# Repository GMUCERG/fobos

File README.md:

FOBOS
=====

Flexible Open-source workBench fOr Side-channel analysis (FOBOS) is an "acquisition to analysis" solution which includes all necessary software to control the device under test (attack) (DUT), trigger the oscilloscope, obtain the measurements and analyze them using several power analysis techniques.

FOBOS splits the Side Channel Analysis (SCA) setup into a control board, a DUT, and the SCA workstation. The firmware for the control board can be found in the folder `control`. The hardware description language files required to adapt a cryptographic algorithm to a particular FOBOS DUT are in the folder `DUT`. The `hardware` folder on the other hand contains circuit board design files for FOBOS boards such as the FOBOS Shield and several FOBOS DUTs. The `software` folder contains the scripts to run FOBOS. These python scripts run partially on the SCA workstation within a Jupyter notebook and partially on the Pynq DUT. The `docs` folder contains the FOBOS documentation.

Please cite as: 
```bibtex
@inproceedings{fobos3,
author = {Ferrufino, Eduardo and Beckwith, Luke and Abdulgadir, Abubakr and Kaps, Jens-Peter},
title = {{FOBOS} 3: An Open-Source Platform for Side-Channel Analysis and Benchmarking},
year = {2023},
isbn = {9798400702624},
publisher = {Association for Computing Machinery},
address = {New York, NY, USA},
url = {https://doi.org/10.1145/3605769.3623987},
doi = {10.1145/3605769.3623987},
pages = {5--14},
keywords = {hardware security, lightweight cryptography, side-channel analysis, benchmarking},
location = {, Copenhagen, Denmark, },
series = {ASHES '23}
}
```

FOBOS Control Board
-------------------
* `control`
   VHDL sources for configuring the FOBOS Control Boards. Requires Xilinx Vivado 2022.1.
   * `pynqctrl`
     Using a Digilent Inc PYNQ-Z1 or TUL PYNQ-Z2 as control board and either the FOBOS Shield or an oscilloscope for measurements.
   * `ip-repo` 
     Modules used by either control board.

FOBOS DUT
---------
* `dut`
  VHDL sources for FOBOS wrapper and pin assignments to prepare a DUT for instantiating a target algorithm.
  * `fpga_wrapper`
    Source code of the FOBOS wrapper common to all FPGA targets and the constraint files for the supported DUTs.
  * `example_cores`
    Contains implementations of example algorithms required for the tutorials.
 
FOBOS Hardware
--------------
* `hardware`
  Printed Circuit Board design files for FOBOS boards. Requires KiCad.
  * `fobos-shield`
    FOBOS Shield is a data aqcuisition and benchmarking boad that can be attached to the PYNQ-Z1 board.
  * `fobos-shield-Z2`
    FOBOS Shield is a data aqcuisition and benchmarking boad that can be attached to the PYNQ-Z2 board.
  * `fobos-mtc`
    FOBOS Multi Target Connector allows simple connection of DUT boards with PMOD connectors to the FOBOS Shield.
  * `fobos-dut`
    Contains folders for each FOBOS DUT.

FOBOS Software
--------------
* `software`
  FOBOS is controlled by a series of Python 3 scripts. 

  * `foboslib` contains all common FOBOS functions.
  * `notebooks` contains Jupyter notebooks that run within Jupyter Lab on the SCA workstation.
  * `lwc_tools` contains tools to make the GMU LWC Hardware API compatible with FOBOS.
  * `firmware` contains software that runs on FOBOS Control.

Documentation
-------------

* `docs` 
  Contains the sources for the Sphinx based documentation of FOBOS and the makefile to compile it.
  You can also read it at https://cryptography.gmu.edu/documentation/fobos3/index.html
  
License
-------

Copyright 2024 Cryptographic Engineering Research Group (CERG)

Licensed under the Apache License, Version 2.0 (the "License");
you may not use this file except in compliance with the License.
You may obtain a copy of the License at

    http://www.apache.org/licenses/LICENSE-2.0

Unless required by applicable law or agreed to in writing, software
distributed under the License is distributed on an "AS IS" BASIS,
WITHOUT WARRANTIES OR CONDITIONS OF ANY KIND, either express or implied.
See the License for the specific language governing permissions and
limitations under the License.

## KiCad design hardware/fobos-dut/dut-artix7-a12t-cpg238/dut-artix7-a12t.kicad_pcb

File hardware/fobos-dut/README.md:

FOBOS-DUT Boards
=========
  * `dut-artix7-a12t-cpg238`
    FOBOS FBD-A7 DUT with a Xilinx Artix-7 xc7a12tcpg238 device and power measurement circuitry.

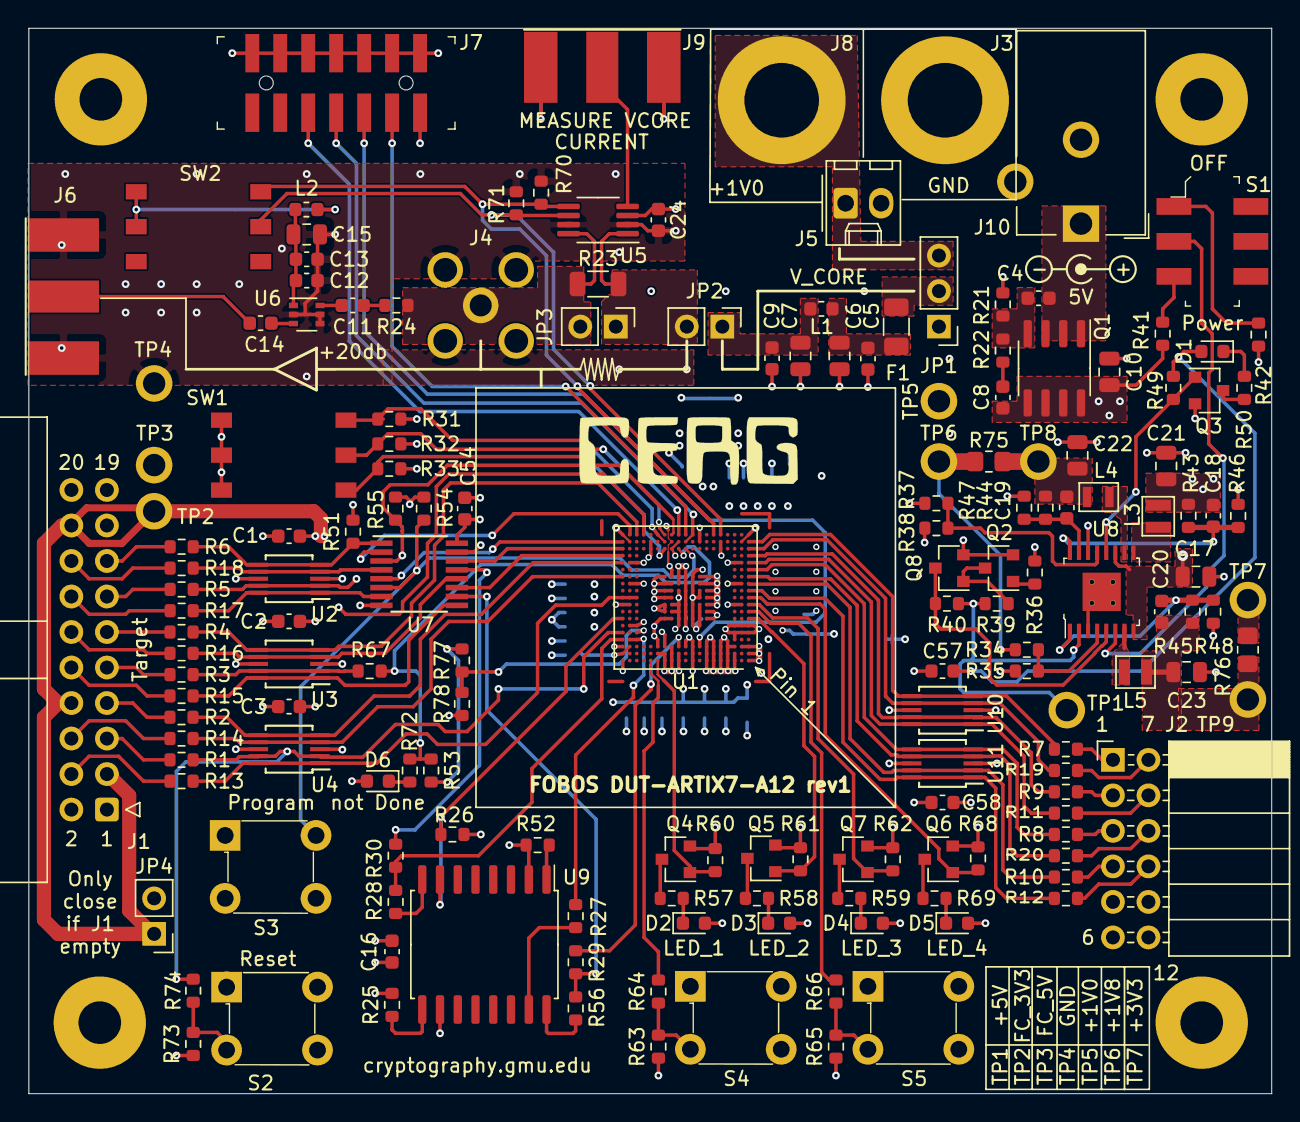
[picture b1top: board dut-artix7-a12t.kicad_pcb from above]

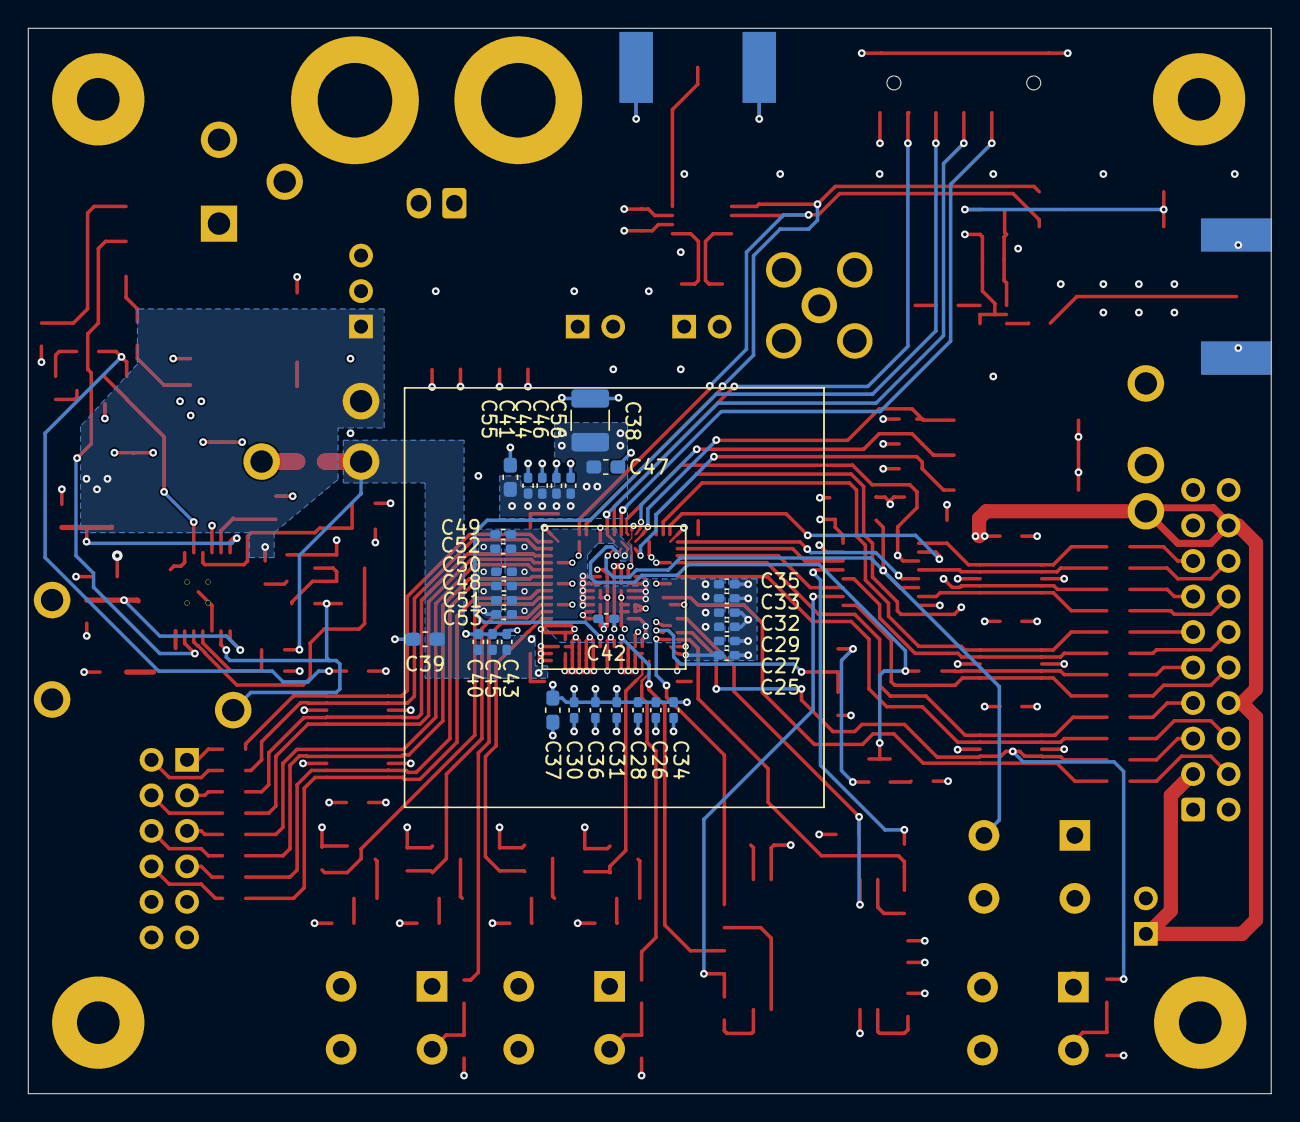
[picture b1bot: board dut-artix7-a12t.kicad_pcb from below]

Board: 4 copper layers, 88.9 x 76.2 mm, 201 parts (31 on the bottom side), 126 nets.

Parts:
C1, C2, C3, C4, C5, C9, C11, C13, C14, C16, C24, C54, C57, C58: 100nF; C_0603_1608Metric
C6, C10, C22, C23: 10uF; C_0805_2012Metric
C7: 47uF6.3V; C_0805_2012Metric
C8: 10nF; C_0603_1608Metric
C12: 4n7; C_0603_1608Metric
C15: 2u2; C_0805_2012Metric
C17, C21: 22uF; C_0805_2012Metric
C18, C19, C20: 20pF; C_0603_1608Metric
C25, C26, C27, C28, C40, C41, C48, C49: 4.7uF; C_0402_1005Metric_Pad0.74x0.62mm_HandSolder
C29, C30, C31, C32, C33, C34, C35, C36, C42, C43, C44, C45, C46, C50, C51, C52, C53, C56: .47uF; C_0402_1005Metric_Pad0.74x0.62mm_HandSolder
C37, C39, C47, C55: 47uF; C_0603_1608Metric_Pad1.08x0.95mm_HandSolder
C38: 100uF; C_1210_3225Metric_Pad1.33x2.70mm_HandSolder
D1, D2, D3, D4, D5, D6: LG_L29K-G2J1-24-Z; LED_0603_1608Metric
F1: MF-MSMF050-2; Fuse_1206_3216Metric
H1, H2, H3, H4: MountingHole; MH_4-40
J1: Target; IDC-Header_2x10_P2.54mm_Horizontal
J2: Pmod 2x6; PinSocket_2x06_P2.54mm_Horizontal_FLipped
J3, J8: 575-8
J4: Glitch; SMA-JOHNSON-142-0701-201
J5: Conn_01x02; Molex_KK-254_AE-6410-02A_1x02_P2.54mm_Vertical
J6, J9: Measure; SMA-JOHNSON-142-0701-801
J7: 0878321420; PinHeader_2x7_P2mm_SMD
J10: Barrel_Jack_Switch; BarrelJack_CUI_PJ-102AH_Horizontal
JP1: Source; PinHeader_1x03_P2.54mm_Vertical
JP2: CurProbe; PinHeader_1x02_P2.54mm_Vertical
JP3: Shunt1R; PinHeader_1x02_P2.54mm_Vertical
JP4: FC3V3_3V3_SHUNT; PinHeader_1x02_P2.54mm_Vertical
L1, L2: 1k/500mA; L_0603_1608Metric
L3: 1.5uH; L_SRN2012
L4: 3.3uH; L_BRC2012
L5: 2.2uH; L_SRN2012
Q1: FDS9435A; SOIC-8_3.9x4.9mm_P1.27mm
Q2, Q8: MMBT3904; SOT-23
Q3, Q4, Q5, Q6, Q7: BSS138; SOT-23
R1, R2, R3, R4, R5, R6, R13, R14, R15, R16, R17, R18: 22R; R_0603_1608Metric
R7, R8, R9, R10, R11, R12, R19, R20, R53, R72: 200R; R_0603_1608Metric
R21: 1M; R_0603_1608Metric
R22: 100R; R_0603_1608Metric
R23: 0R1; R_1206_3216Metric
R24: 49R9; R_0603_1608Metric
R25, R26, R31, R32, R33, R41, R52, R54, R55: 4.7KR; R_0603_1608Metric
R27, R28, R56: 33R; R_0603_1608Metric
R29, R30, R37, R67: 0R; R_0603_1608Metric
R34: 3.48KR; R_0603_1608Metric
R35, R42, R51, R60, R61, R62, R63, R64, R65, R66, R68, R70, R71, R73, R74: 10KR; R_0603_1608Metric
R36, R77, R78: 1KR; R_0603_1608Metric
R38, R39, R40, R49: 100KR; R_0603_1608Metric
R43: 30K; R_0603_1608Metric
R44: 150K; R_0603_1608Metric
R45: 180K; R_0603_1608Metric
R46, R47: 120KR; R_0603_1608Metric
R48: 57.6KR; R_0603_1608Metric
R50: 800R; R_0603_1608Metric
R57, R58, R59, R69: 470R; R_0603_1608Metric
R75, R76: 0.1R; R_0805_2012Metric_Pad1.20x1.40mm_HandSolder
S1: JS202011SCQN; Switch_Slide_JS202011SCQN
S2, S3, S4, S5: 1825910-6; Switch_Tactile_THT_6x6mm
SW1, SW2: SW_DIP_x03; DS04-254-2-03BK-SMT
TP1, TP2, TP3, TP4, TP5, TP6, TP7, TP8, TP9: 5281
U1: XC7A12T-CPG238; Xilinx_CPG238
U2, U3, U4, U10, U11: SP3003-04ATG; MSOP-10_3x3mm_P0.5mm
U5: INA225; MSOP-8_3x3mm_P0.65mm
U6: BGA2801; SOT-363_SC-70-6
U7: TS3A5018DBQR; SSOP-16_4.0x5.0mm_P0.635mm
U8: LTC3569EFE#PBF; TSSOP-16-1EP_W4.40mm
U9: IS25LP256D-JMLE; SOIC-16W_7.5x10.3mm_P1.27mm

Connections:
+1V0: C18.1, C21.1, JP1.1 (A), L3.2, R36.1, R43.2, TP5.1
+1V8: C39.1, C40.1, C43.1, C45.1, R34.2, R75.2, TP6.1, U1.C13, U1.H13, U1.J13
+3V3: C16.1, C25.1, C26.1, C27.1, C28.1, C29.1, C30.1, C31.1, C32.1, C33.1, C34.1, C35.1, C36.1, C37.1, C48.1, C49.1, C50.1, C51.1, C52.1, C53.1, J7.2, JP4.2 (B), R25.2, R26.2, R31.1, R32.1, R33.1, R52.2, R53.2, R54.2, R55.2, R76.2, R77.2, TP7.1, U1.B19, U1.C14, U1.C18, U1.G12, U1.G13, U1.J7, U1.K7, U1.K12, U1.K13, U1.L7, U1.L12, U1.L13, U1.M7, U1.M8, U1.M12, U1.M13, U1.N7, U1.N8, U1.N13, U1.U12, U1.V11, U9.2 (VCC)
+5V: C8.1, C10.1, C17.1, Q1.5 (D), Q1.6 (D), Q1.7 (D), Q1.8 (D), R37.2, R39.2, R40.2, R41.2, TP1.1, U8.2 (SVIN), U8.8 (PVIN1), U8.11 (PVIN2), U8.14 (RT)
/Connectors, IO/CW_HS1: J1.4, R13.2
/Connectors, IO/CW_HS2: J1.6, R14.2
/Connectors, IO/CW_MISO: J1.7, R2.1
/Connectors, IO/CW_MOSI: J1.9, R3.1
/Connectors, IO/CW_PDIC: J1.13, R5.1
/Connectors, IO/CW_PDID: J1.15, R6.1
/Connectors, IO/CW_RST: J1.5, R1.1
/Connectors, IO/CW_SCK: J1.11, R4.1
/Connectors, IO/CW_TARG1: J1.10, R15.2
/Connectors, IO/CW_TARG2: J1.12, R16.2
/Connectors, IO/CW_TARG3: J1.14, R17.2
/Connectors, IO/CW_TARG4: J1.16, R18.2
/FPGA 1/DIN: R28.1, R30.2, U1.D19
/FPGA 1/FCS: R26.1, U1.G19, U9.7 (CE#)
/FPGA 1/MOSI: R27.1, U1.D17, U1.D18
/FPGA 1/PUDC: R77.1, R78.2, U1.E17
/FPGA Programming/CCLK: R29.2, U1.C11
/FPGA Programming/MODE_1: R32.2, SW1.4, U1.W13
/FPGA Programming/MODE_2: R33.2, SW1.6, U1.U13
/FPGA Programming/TCK: J7.6, U1.C8
/FPGA Programming/TDI: J7.10, U1.W11
/FPGA Programming/TMS: J7.4, U1.W10
/Power/EN2: Q8.3 (C), R40.1, U8.5 (EN2)
/Power/EN3: R34.1, R35.2, U8.4 (EN3)
/Power/FB1: C18.2, R43.1, R46.1, U8.16 (FB1)
/Power/FB2: C19.2, R44.1, R47.1, U8.15 (FB2)
/Power/FB3: C20.2, R45.1, R48.1, U8.1 (FB3)
/Power/MODE: R37.1, R38.2, U8.13 (MODE)
/Power/SW1: L3.1, U8.9 (SW1)
/Power/SW2: L4.1, U8.10 (SW2)
/Power/SW3: L5.1, U8.7 (SW3)
/Power/pre1V8: C19.1, C22.1, L4.2, R44.2, R75.1, TP8.1
/Power/pre3V3: C20.1, C23.1, L5.2, R45.2, R76.1, TP9.1
FC2D_CLK: R14.1, U1.N19, U4.4 (IO3)
FC2D_HS: R4.2, U1.W17, U3.5 (IO4)
FC_3V3: C1.2, C2.2, C3.2, C24.1, C54.1, C57.2, C58.2, D1.2 (A), D2.2 (A), D3.2 (A), D4.2 (A), D5.2 (A), J1.3, J1.8, J1.18, J2.6, J2.12, JP4.1 (A), L2.1, R49.1, S2.1, S4.1, S5.1, SW2.4, SW2.6, TP2.1, U2.3 (VCC), U3.3 (VCC), U4.3 (VCC), U5.3 (Vs), U7.16 (V+), U10.3 (VCC), U11.3 (VCC)
FC_5V: C4.1, J1.1, J1.20, J10.1, Q1.1 (S), Q1.2 (S), Q1.3 (S), TP3.1
FC_DIO0: R15.1, U3.1 (IO1), U7.9 (COM3)
FC_DIO0_MUX: U1.T19, U7.11 (NC3)
FC_DIO1: R16.1, U3.4 (IO3), U7.12 (COM4)
FC_DIO1_MUX: U1.U19, U7.14 (NC4)
FC_DIO2: R17.1, U2.1 (IO1), U7.7 (COM2)
FC_DIO2_MUX: U1.V19, U7.5 (NC2)
FC_DIO3: R18.1, U2.4 (IO3), U7.4 (COM1)
FC_DIO3_MUX: U1.W18, U7.2 (NC1)
FC_IO: R2.2, U1.R19, U4.5 (IO4)
FC_PROG: R6.2, R51.2, U2.5 (IO4), U7.1 (IN)
FC_RST: R1.2, R74.2, U1.E19, U4.2 (IO2)
FD2C_CLK: R13.1, U1.K17, U1.K18, U1.K19, U4.1 (IO1)
FD2C_HS: R5.2, U1.W16, U2.2 (IO2)
FD_TF: R3.2, R67.1, U3.2 (IO2)
GND: C1.1, C2.1, C3.1, C5.2, C6.2, C7.2, C9.2, C10.2, C12.2, C13.2, C15.2, C16.2, C17.2, C21.2, C22.2, C23.2, C24.2, C25.2, C26.2, C27.2, C28.2, C29.2, C30.2, C31.2, C32.2, C33.2, C34.2, C35.2, C36.2, C37.2, C38.2, C39.2, C40.2, C41.2, C42.2, C43.2, C44.2, C45.2, C46.2, C47.2, C48.2, C49.2, C50.2, C51.2, C52.2, C53.2, C54.2, C55.2, C56.2, C57.1, C58.1, D6.2, J1.2, J1.17, J1.19, J2.5, J2.11, J3.1, J4.2 (Ext), J5.2, J6.2 (Ext), J7.1, J7.3, J7.5, J7.7, J7.9, J7.11, J7.13, J9.2 (Ext), J10.2, Q2.2 (E), Q3.2 (S), Q4.2 (S), Q5.2 (S), Q6.2 (S), Q7.2 (S), Q8.2 (E), R21.1, R35.1, R38.1, R42.1, R46.2, R47.2, R48.2, R51.1, R60.1, R61.1, R62.1, R63.1, R65.1, R68.1, R70.1, R71.1, R73.1, R78.1, S3.4, SW1.1, SW1.3, SW1.5, TP4.1, U1.A1, U1.A3, U1.A4, U1.A5, U1.A6, U1.A7, U1.A9, U1.A11, U1.A12, U1.A13, U1.A19, U1.B1, U1.B3, U1.B4, U1.B5, U1.B6, U1.B7, U1.B9, U1.B11, U1.B12, U1.B13, U1.B14, U1.C1, U1.C2, U1.C3, U1.C4, U1.C5, U1.C6, U1.C7, U1.C9, U1.C10, U1.C12, U1.C19, U1.D3, U1.E1, U1.E2, U1.E3, U1.F1, U1.F2, U1.F3, U1.F17, U1.F18, U1.G7, U1.G8, U1.G9, U1.G11, U1.H7, U1.H8, U1.H9, U1.H11, U1.H12, U1.J2, U1.J3, U1.J8, U1.J9, U1.J11, U1.J12, U1.J18, U1.J19, U1.K8, U1.L8, U1.L9, U1.L11, U1.M2, U1.M3, U1.M9, U1.M17, U1.M18, U1.N9, U1.N12, U1.R2, U1.R3, U1.R17, U1.R18, U1.U5, U1.U15, U1.V2, U1.V5, U1.V8, U1.V12, U1.V15, U1.V18, U1.W1, U1.W8, U1.W19, U2.8 (GND), U3.8 (GND), U4.8 (GND), U5.2 (GND), U5.7 (Ref), U6.2 (G), U6.4 (G), U6.5 (G), U7.8 (GND), U7.15 (EN#), U8.3 (SGND), U8.17 (EPAD), U9.10 (GND), U10.8 (GND), U11.8 (GND)
JA1: R7.2, U1.V1, U10.5 (IO4)
JA2: R9.2, U1.T1, U10.2 (IO2)
JA3: R8.2, U1.P1, U11.5 (IO4)
JA4: R10.2, U1.M1, U11.2 (IO2)
JA7: R19.1, U1.U1, U10.4 (IO3)
JA8: R11.1, U1.R1, U10.1 (IO1)
JA9: R20.1, U1.N1, U11.4 (IO3)
JA10: R12.1, U1.L1, U11.1 (IO1)
MODE_0: R31.2, SW1.2, U1.V13, U1.W14
unnamed: C5.1, C6.1, F1.1, L1.2
unnamed: C8.2, R22.1
unnamed: C11.1, U6.6
unnamed: C11.2, R24.1
unnamed: C14.2, U6.3
unnamed: D1.1 (K), R50.1
unnamed: D2.1 (K), R57.1
unnamed: D3.1 (K), R58.1
unnamed: D4.1 (K), R59.1
unnamed: D5.1 (K), R69.1
unnamed: D6.1, R72.1
unnamed: J2.1, R7.1
unnamed: J2.2, R9.1
unnamed: J2.3, R8.1
unnamed: J2.4, R10.1
unnamed: J2.7, R19.2
unnamed: J2.8, R11.2
unnamed: J2.9, R20.2
unnamed: J2.10, R12.2
unnamed: J5.1, J8.1, JP1.3 (B)
unnamed: C14.1, J6.1 (In)
unnamed: F1.2, JP1.2 (C)
unnamed: C7.1, C9.1, JP2.1 (A), L1.1
unnamed: JP2.2 (B), JP3.1 (A), R23.2, U5.1 (Vin+)
unnamed: C4.2, Q1.4 (G), R21.2, R22.2
unnamed: Q2.1 (B), R36.2
unnamed: Q2.3 (C), Q8.1 (B), R39.1
unnamed: Q3.3 (D), R50.2
unnamed: Q4.3 (D), R57.2
unnamed: Q5.3 (D), R58.2
unnamed: Q6.3 (D), R69.2
unnamed: Q7.3 (D), R59.2
unnamed: R41.1, S1.3
unnamed: R42.2, S1.1
unnamed: R63.2, R64.1, S4.3
unnamed: R65.2, R66.1, S5.3
unnamed: R73.2, R74.1, S2.3
unnamed: C12.1, C13.1, C15.1, L2.2, U6.1 (Vcc)
unnamed: R52.1, U9.1 (HOLD#)
unnamed: R56.2, U9.16 (SCK)
unnamed: R27.2, U9.15 (SI)
unnamed: R28.2, U9.8 (SO)
unnamed: R25.1, U9.9 (WP#)
ON_OFF: S1.2, U8.6 (EN1)
PGOOD: Q3.1 (G), R49.2, U8.12 (PGOOD)
SW_CLK: R29.1, R56.1, U7.10 (NO3)
SW_DIN: R30.1, U7.13 (NO4)
SW_DONE: R53.1, R67.2, R72.2, U1.U11
SW_INIT_B: R55.1, U1.W12, U7.3 (NO1)
SW_PROGRAM_B: R54.1, S3.2, U1.U10, U7.6 (NO2)
TDO: J7.8, U1.V10, U1.W9
USER_BTN_1: R64.2, U1.A15
USER_BTN_2: R66.2, U1.H1
USER_LED_1: Q4.1 (G), R60.2, U1.A14
USER_LED_2: Q5.1 (G), R61.2, U1.G1
USER_LED_3: Q7.1 (G), R62.2, U1.J1
USER_LED_4: Q6.1 (G), R68.2, U1.K1
VCCINT: C38.1, C41.1, C42.1, C44.1, C46.1, C47.1, C55.1, C56.1, J4.1 (In), JP3.2 (B), R23.1, R24.2, U1.G10, U1.H10, U1.J10, U1.L10, U1.M10, U1.M11, U1.N10, U1.N11, U5.8 (Vin-)
VCORE_CURRENT: J9.1 (In), U5.4 (Out)
VCORE_CURRENT_GAIN_0: R70.2, SW2.5, U1.W6, U5.5 (GS0)
VCORE_CURRENT_GAIN_1: R71.2, SW2.3, U1.W5, U5.6 (GS1)

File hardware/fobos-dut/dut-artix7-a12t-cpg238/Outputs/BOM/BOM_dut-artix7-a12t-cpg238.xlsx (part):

Artix-7 DUT
Ref# | Qty. | Value | Size | Mouser # | Mfr. # | Manufacturer | Description
R29 R30 R37 R67 | 4 | 0R | 0603 | 603-RC0603JR-070RL | RC0603JR-070RL | Yageo | Thick Film Resistors - SMD 0 Ohms 100 mW 0603 5%
R23 | 1 | 0R1 | 1206 | 71-WSL1206R1000DEA | WSL1206R1000DEA | Vishay | Current Sense Resistors - SMD 1/4watt .1ohms .5%
R24 | 1 | 49R9 | 0603 | 652-CR0603FX-49R9ELF | CR0603-FX-49R9ELF | Bourns | Thick Film Resistors - SMD 49.9 ohm 1%
R75 R76 | 2 | 0R1 | 0805 | 588-KDV08FR100ET | KDV08FR100ET | Ohmite | Current Sense Resistors - SMD 0.1 ohm 0805 1% 0.25W
R22 | 1 | 100R | 0603 | 603-RC0603FR-13100RL | RC0603FR-13100RL | Yageo | Thick Film Resistors - SMD 100 OHM 1%
R36 R77 R78 | 3 | 1k | 0603 | 603-RC0603FR-071KL | RC0603FR-071KL | Yageo | Thick Film Resistors - SMD 1K OHM 1%
R35 R42 R43 R44 R45 R51 R60 R61 R62 R63 R64 R65 R66 R68 R70 R71 R73 R74 | 18 | 10k | 0603 | 603-RC0603FR-0710KL | RC0603FR-0710KL | Yageo | Thick Film Resistors - SMD 10K OHM 1%
R38 R39 R40 R49 | 4 | 100k | 0603 | 652-CR0603-FX-103ELF | CR0603-FX-1003ELF | Bourns | Thick Film Resistors - SMD 100K 1% 1/10 WATT
R21 | 1 | 1M | 0603 | 652-CR0603FX-1004ELF | CR0603-FX-1004ELF | Bourns | Thick Film Resistors - SMD 1M 1% 1/10W
R46 R47 | 2 | 120k | 0603 | 603-RC0603FR-13120KL | RC0603FR-13120KL | Yageo | Thick Film Resistors - SMD 120 kOhms 100-200 mW 0603 1%
R7 R8 R9 R10 R11 R12 R19 R20 R53 R72 | 10 | 200R | 0603 | 603-RC0603FR-07200RL | RC0603FR-07200RL | Yageo | Thick Film Resistors - SMD 200 OHM 1%
R1 R2 R3 R4 R5 R6 R13 R14 R15 R16 R17 R18 | 12 | 22R | 0603 | 603-RC0603FR-0722RL | RC0603FR-0722RL | Yageo | Thick Film Resistors - SMD 22 OHM 1%
R27 R28 R56 | 3 | 33R, 0.5% | 0603 | 667-ERA-3AHD330V | ERA-3AHD330V | Panasonic | Thin Film Resistors - SMD 0603 33ohms 50ppm 0.5% AEC-Q200
R34 | 1 | 3k48 | 0603 | 603-RC0603FR-073K48L | RC0603FR-073K48L | Yageo | Thick Film Resistors - SMD 3.48 kOhms 100mW 0603 1%
R57 R58 R59 R69 | 4 | 470R | 0603 | 603-RC0603FR-10470RL | RC0603FR-10470RL | Yageo | Thick Film Resistors - SMD 470 OHM 1%
R25 R26 R31 R32 R33 R41 R52 R54 R55 | 9 | 4k7 | 0603 | 603-RC0603FR-134K7L | RC0603FR-134K7L | Yageo | Thick Film Resistors - SMD 4.7 kOhms 100-200mW 0603 1%
R48 | 1 | 57k6 | 0603 | 652-CR0603FX-5762ELF | CR0603-FX-5762ELF | Bourns | Thick Film Resistors - SMD 57.6K ohm 1%
R50 | 1 | 800R | 0603 | 603-RC0603FR-07806RL | RC0603FR-07806RL | Yageo | Thick Film Resistors - SMD 806 Ohms 100 mW 0603 1%
C8 | 1 | 10nF | 0603 | 603-CS0603KRX79BB103 | CS0603KRX7R9BB103 | Yageo | Multilayer Ceramic Capacitors MLCC - SMD/SMT 10 nF 50 V 10% Ceramic Capacitors
C1 C2 C3 C4 C5 C9 C11 C13 C14 C16 C24 C54 C57 C58 | 14 | 100nF | 0603 | 77-VJ0603Y104JXQPBC | VJ0603Y104JXQPW1BC | Vishay / Vitramon | Multilayer Ceramic Capacitors MLCC - SMD/SMT 0603 0.1uF 10volts X7R 5%
C6 C10 C22 C23 | 4 | 10uF | 0805 | 81-GRM21BC81C106MA3L | GRM21BC81C106MA73L | Murata Electronics | Multilayer Ceramic Capacitors MLCC - SMD/SMT 0805 10uF 16volts X6S 20%
C18 C19 C20 | 3 | 20pF | 0603 | 80-C0603C200K8HACTU | C0603C200K8HACTU | KEMET | Multilayer Ceramic Capacitors MLCC - SMD/SMT 10V 20pF X8R 0603 10%
C15 | 1 | 2u2F | 0805
C17 C21 | 2 | 22uF | 0805 | 187-CL21A226KQCLRNC | CL21A226KQCLRNC | Samsung | Multilayer Ceramic Capacitors MLCC - SMD/SMT 22uF+/-10% 6.3V X5R 2012
C12 | 1 | 4n7F | 0603 | 710-885012206087 | 885012206087 | Wurth Electronics | Multilayer Ceramic Capacitors MLCC - SMD/SMT WCAP-CSGP 4700pF 0603 10% 50V MLCC
C29 C30 C31 C32 C33 C34 C35 C36 C42 C43 C44 C45 C46 C50 C51 C52 C53 C56 | 18 | 470nF | 0402 | 963-JMK105BJ474KV-F | JMK105BJ474KV-F | Taiyo Yuden | CAP CER 0.47UF 6.3V X5R 0402
C25 C26 C27 C28 C40 C41 C48 C49 | 8 | 4.7uF | 0402 | 81-GRM155R60J475ME8J | GRM155R60J475ME87J | Murata Electronics | CAP CER 4.7UF 6.3V X5R 0402
C37 C39 C47 C55 | 4 | 47uF | 0603 | 81-GRM21BR60J476ME5K | GRM21BR60J476ME15K | Murata Electronics | Multilayer Ceramic Capacitors MLCC - SMD/SMT 0805 47uF 6.3volts
C7 | 1 | 47uF | 0805 | 81-GRT21BR60J476ME3L | GRT21BR60J476ME13L | Murata Electronics | Multilayer Ceramic Capacitors MLCC - SMD/SMT 47UF 6.3V 20% 0805
C38 | 1 | 100uF | 1210 | 81-GRM32ER61A107ME0L | GRM32ER61A107ME0L | Murata Electronics | Multilayer Ceramic Capacitors MLCC - SMD/SMT 1210 100uF 10V
L1 L2 | 2 | 1k/500mA | 0603 | 963-FBMH1608HM102-T | FBMH1608HM102-T | Taiyo Yuden | Ferrite Beads HI CUR CHIP BD 0603 1000OHMS 25%
L3 | 1 | 1.5uH |  | 652-SRN2012-1R5M | SRN2012-1R5M | Bourns Inc. | FIXED IND 1.5UH 1.8A 108MOHM SMD
L4 | 1 | 3.3uH |  | 963-BRC2012T3R3MD | BRC2012T3R3MD | Taiyo Yuden | FIXED IND 3.3UH 870MA 221MOHM SM
L5 | 1 | 2.2uH |  | 652-SRN2010-2R2M | SRN2010-2R2M | Bourns Inc. | FIXED IND 2.2UH 1.7A 170MOHM SMD
D1 D2 D3 D4 D5 D6 | 6 | green | 0603 | 604-APT1608CGCK | APT1608CGCK | Kingbright | Standard LEDs - SMD Green Water Clear 570nm 40mcd 120deg
Q3 Q4 Q5 Q6 Q7 | 5 | BSS138L | SOT-23-3 | 512-BSS138L | BSS138L | ON Semiconductor | MOSFET 0.20A, 50V N-Channel SOT-23 MOSFET
Q1 | 1 | FDS9435A | SOIC-8 | 512-FDS9435A | FDS9435A | ON Semiconductor/Fairchild | MOSFET SO-8 SGL P-CH -30V
Q2 Q8 | 2 | 3904 | SOT-23-3 | 863-MMBT3904LT1G | MMBT3904LT1G | ON Semiconductor | Bipolar Transistors - BJT NPN GENERAL PURPOSE
U8 | 1 | LTC3569EFE#PBF | 16TSSOP | LTC3569EFE#PBF | LTC3569EFE#PBF | Analog Devices Inc. | Switching Voltage Regulators Programmable 1.2A and 2X600mA, Triple Buck Regulat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
U5 | 1 | INA225 | MSOP-8 | 595-INA225AIDGKT | INA225AIDGKT | Texas Instruments | Current Sense Amplifiers 36V Bidir 0-Drift Ser Crnt-Shunt Mon
U7 | 1 | TS3A5018DBQR | 16SSOP | 595-TS3A5018DBQR | TS3A5018DBQR | Texas Instruments | Analog Switch ICs 10-Ohm Quad SPDT Analog Switch
U9 | 1 | IS25LP256D-JMLE | 16SOIC | IS25LP256D-JMLE | IS25LP256D-JMLE | ISSI, Integrated Silicon Solution Inc | NOR Flash 256M 3V 166MHZ Serial Flash
U6 | 1 | BGA2801 | SOT-363 | 771-BGA2801115 | BGA2801,115 | NXP USA Inc. | RF Amplifier 6CH MMIC Amp 3.8 dB 3.3V 14.3mA 2.8GHz
U1 | 1 | XC7A12T-cpg238 | CPG238 | 217-XC7A12T-1CPG238C | XC7A12T-1CPG238C | Xilinx | FPGA - Field Programmable Gate Array XC7A12T-1CPG238C
F1 | 1 | MF-MSMF050-2 | 1206 | 667-ERB-RG2R00V | ERB-RG2R00V | Panasonic Electronic Components | FUSE BOARD MOUNT 2A 63VDC 1206
U2 U3 U4 U10 U11 | 5 | Fuse | MSOP-10 | 576-SP3003-04ATG | SP3003-04ATG | Littelfuse | ESD Suppressors / TVS Diodes 4 Ch 8kV 0.65pF SPA
J10 | 1 | Barrel Jack |  | 490-PJ-102AH | PJ-102AH | CUI | DC Power Connectors Power Jacks
J4 | 1 | SMA Edge |  | 530-142-0701-801 | 142-0701-801 | Johnson / Cinch Connectivity Solutions | RF Connectors / Coaxial Connectors PC END MT JCK GLD .062" BOARD THICK
J6 J9 | 2 | SMA Vertical |  | 712-CONSMA008-G | CONSMA008-G | Linx Technologies | RF Connectors / Coaxial Connectors SMA Female PCB Mnt, Extended, Gold
J1 | 1 | Shrd Hdr | 2x10 | 517-30320-5002 | 30320-5002HB | 3M Electronic Solutions Division | Headers & Wire Housings 20P R/A 4WALL GLDFL
JP1, JP2, JP3, JP4 | 1 | Pin Header | 1x36 | 649-68001-236HLF | 68001-236HLF | Amphenol FCI | Headers & Wire Housings 36P HDR
J5 | 1 | Molex | 1x2-P2.54mm | 538-22-11-2022 | 22-11-2022 | Molex | Connector_Molex:Molex_KK-254_AE-6410-02A_1x02_P2.54mm_Vertical, gold
J7 | 1 | Shrd Hdr | 2x7 2mm | 538-87832-1420 | 878321420 | Molex | Headers & Wire Housings 14P SMD PB FREE SHRD
J3 J8 | 2 | 575-8 |  | 534-575-8 | 575-8 | Keystone Electronics | CONN BANANA JACK SOLDER
J2 | 1 | Pin Socket | 2x6 90 deg | 200-SSW10602FDRA | SSW-106-02-F-D-RA | Samtec | Board to Board & Mezzanine Connectors Tiger Buy Socket Strip with PCB Tails, 0.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
TP1 TP2 TP3 TP4 TP5 TP6 TP7 TP8 TP9 | 9 | 5281 |  | 534-5281 | 5281 | Keystone Electronics | Circuit Board Hardware - PCB TEST POINT BLACK MULTIPURPOSE
S1 | 1 | JS202011SCQN |  | 611-JS202011SCQN | JS202011SCQN | C&K | SWITCH SLIDE DPDT 300MA 6V
S2 S3 S4 S5 | 4 | 1825910-6 |  |  | 1825910-6 | TE Connectivity ALCOSWITCH Switches | SWITCH TACTILE SPST-NO 0.05A 24V
SW1 SW2 | 2 | SW_DIP_x03 |  | 490-DS04254203BK-SMT | DS04-254-2-03BK-SMT | CUI Devices | DIP SWITCH, SPST, 2.54 PITCH, FL
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
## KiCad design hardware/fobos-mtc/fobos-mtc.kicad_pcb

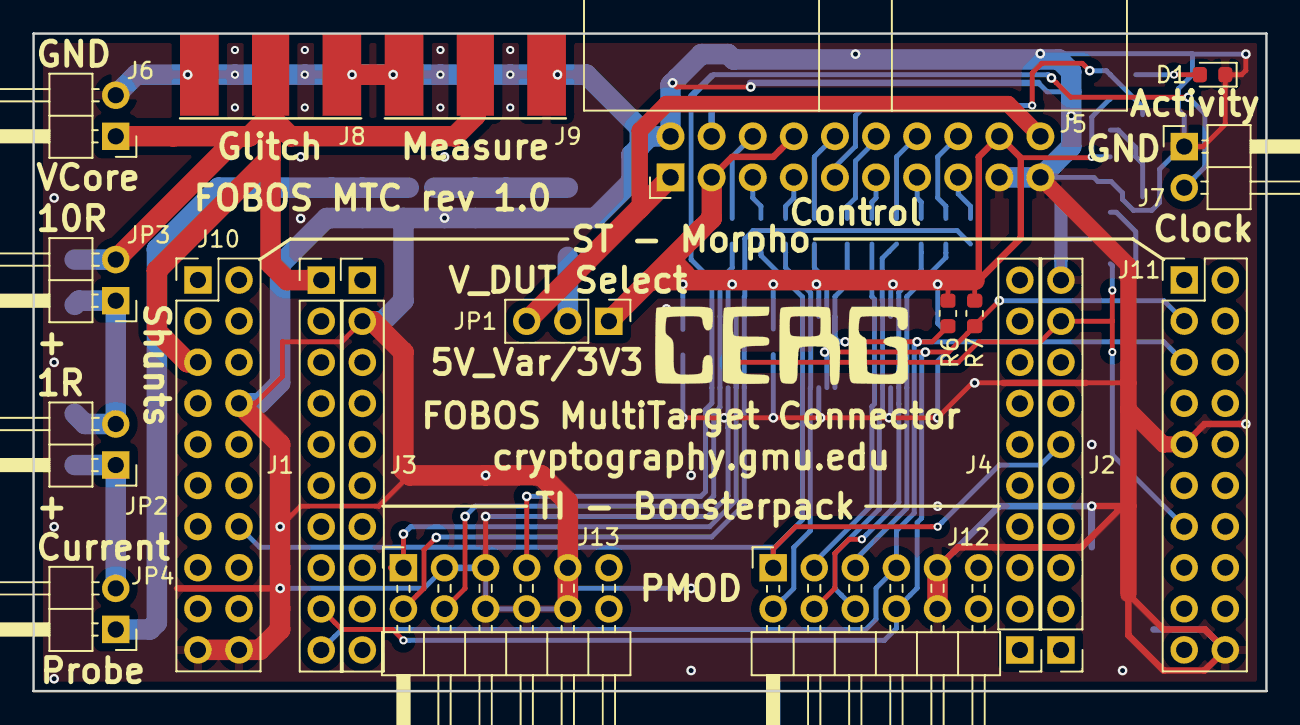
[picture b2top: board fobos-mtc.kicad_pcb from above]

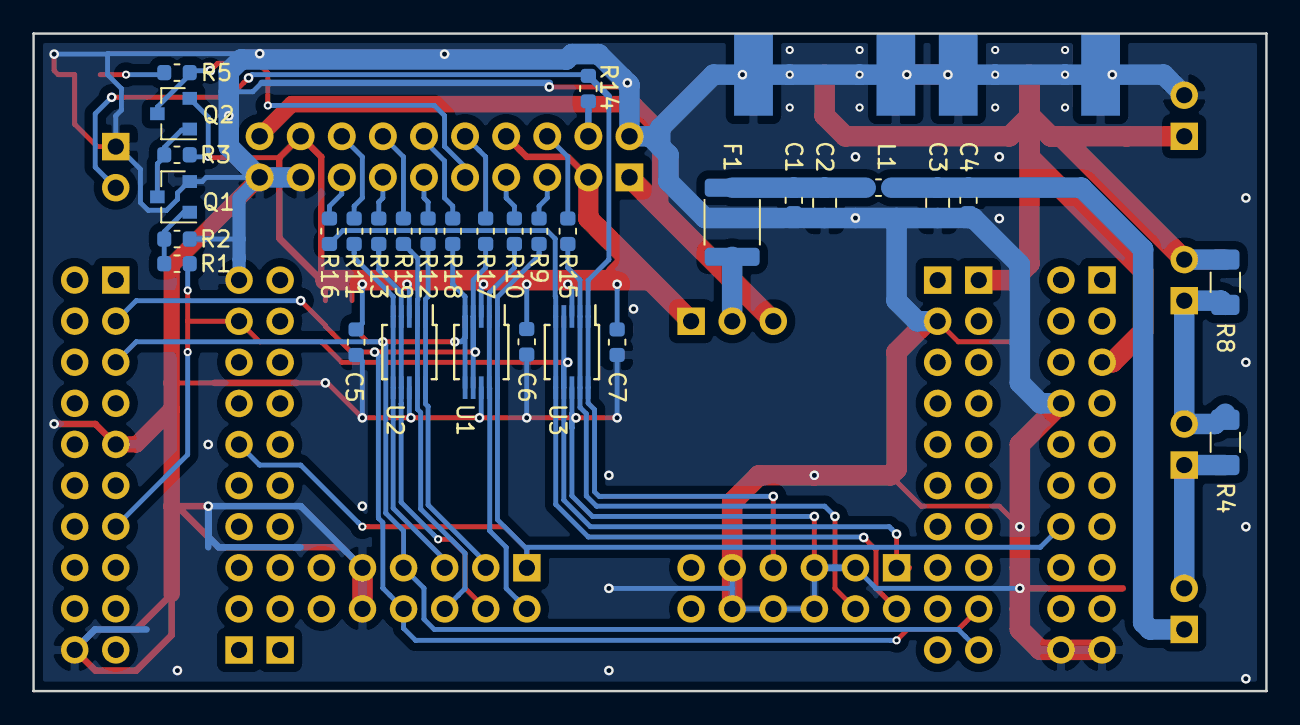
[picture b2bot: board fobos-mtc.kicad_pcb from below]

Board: 2 copper layers, 76.2 x 40.6 mm, 51 parts (31 on the bottom side), 36 nets.

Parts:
C1, C4, C5, C6, C7: 100nF; C_0603_1608Metric
C2: 10uF; C_0805_2012Metric
C3: 47uF6.3V; C_0805_2012Metric
D1: Activity; LED_0603_1608Metric
F1: MF-MSMF050-2; Fuse_1812_4532Metric
J1, J2, J3, J4: Conn_01x10; PinHeader_1x10_P2.54mm_Vertical
J5: Target; IDC-Header_2x10_P2.54mm_Horizontal
J6: Conn_01x02; PinHeader_1x02_P2.54mm_Horizontal
J7: clk; PinHeader_1x02_P2.54mm_Horizontal
J8: Glitch; SMA-JOHNSON-142-0701-801
J9: Measure; SMA-JOHNSON-142-0701-801
J10, J11: Conn_02x10_Odd_Even; PinSocket_2x10_P2.54mm_Vertical-flipped
J12, J13: Conn_02x06_Top_Bottom; PinHeader_2x06_P2.54mm_Horizontal-flipped
JP1: Source; PinHeader_1x03_P2.54mm_Vertical
JP2: Shunt1R; PinHeader_1x02_P2.54mm_Horizontal
JP3: Shunt10R; PinHeader_1x02_P2.54mm_Horizontal
JP4: CurProbe; PinHeader_1x02_P2.54mm_Horizontal
L1: 1k/500mA; L_0603_1608Metric
Q1: BSS138; SOT-23
Q2: BSS84; SOT-23
R1, R9, R10, R11, R12, R13, R14, R15, R16, R17, R18, R19: 22R; R_0603_1608Metric
R2, R3, R6, R7: 10k; R_0603_1608Metric
R4: 1R; R_1206_3216Metric
R5: 470R; R_0603_1608Metric
R8: 10R; R_1206_3216Metric
U1, U2, U3: SP3003-04ATG; MSOP-10_3x3mm_P0.5mm

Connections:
/dutconnect/CV_RST: J5.5, R9.1
/dutconnect/CW_HS1: J5.4, R14.2
/dutconnect/CW_HS2: J5.6, R15.2
/dutconnect/CW_MISO: J5.7, R10.1
/dutconnect/CW_PDIC: J5.13, R13.1
/dutconnect/CW_PDID: J5.15, R16.1
/dutconnect/CW_SCK: J5.11, R12.1
/dutconnect/CW_TARG1: J5.10, R17.2
/dutconnect/CW_TARG2: J5.12, R18.2
/dutconnect/CW_TARG3: J5.14, R19.2
/dutconnect/CW_TARG4: J5.16, R11.2
Aux: J13.7, R16.2, U3.5, U3.6
CLK_C2D: J13.8, R15.1, U3.2, U3.9
CLK_D2C: J7.2, J13.4, R14.1, U3.1, U3.10
CW_3V3: C5.1, C6.1, C7.1, J5.3, J5.8, J5.18, JP1.1, Q2.2, R3.1, R6.2, R7.2, U1.3, U2.3, U3.3
CW_5V: J5.1, J5.20, JP1.3
DIO0: J1.9, J11.3, J12.10, R7.1, R17.1, U1.4, U1.7
DIO1: J1.10, J11.5, J12.4, R6.1, R18.1, U1.5, U1.6
DIO2: J12.9, R19.1, U2.2, U2.9
DIO3: J12.3, R11.1, U2.5, U2.6
GND: C1.2, C2.2, C3.2, C4.2, C5.2, C6.2, C7.2, D1.1, J2.10, J3.2, J5.2, J5.17, J5.19, J6.2, J7.1, J8.2, J9.2, J10.8, J10.19, J10.20, J11.9, J11.20, J12.5, J12.11, J13.2, J13.3, J13.5, J13.9, J13.10, J13.11, Q1.2, R2.2, U1.8, U2.8, U3.8
IO: J12.7, R10.2, U1.2, U1.9
unnamed: C1.1, C2.1, F1.1, L1.2
unnamed: D1.2, R5.2
unnamed: F1.2, JP1.2
unnamed: JP2.1, JP4.2, R4.2
unnamed: JP2.2, JP3.1, R4.1, R8.2
unnamed: Q1.1, R1.1, R2.1
unnamed: Q1.3, Q2.1, R3.2
RST: J2.6, J10.14, J12.1, R9.2, U1.1, U1.10
Ready: J12.2, R12.2, U2.1, U2.10
TF: J5.9, Q2.3, R5.1
TFD: J2.9, J11.13, J13.1, R1.2, U3.4, U3.7
V_XBD: J1.1, J6.1, J8.1, J9.1, J10.5, JP3.2, R8.1
Valid: J12.8, R13.2, U2.4, U2.7
XBD_AVCC: C3.1, C4.1, JP4.1, L1.1

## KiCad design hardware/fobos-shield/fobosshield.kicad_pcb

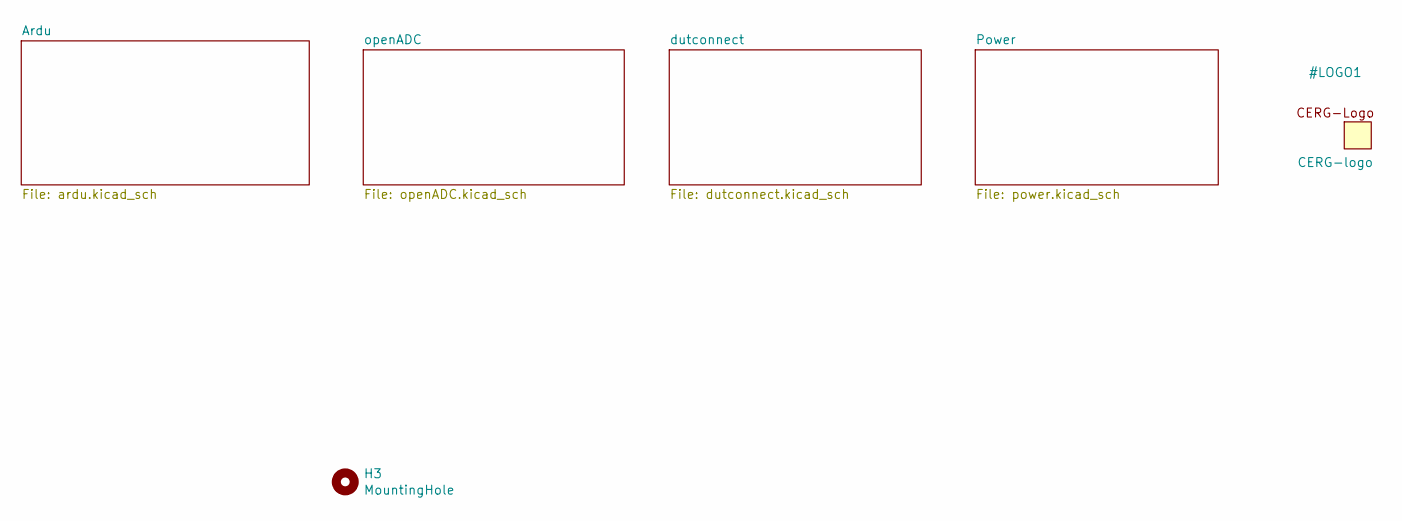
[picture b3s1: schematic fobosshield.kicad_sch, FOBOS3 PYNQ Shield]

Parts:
H3: MountingHole; MountingHole_3.2mm_M3_DIN965_Pad_TopBottom

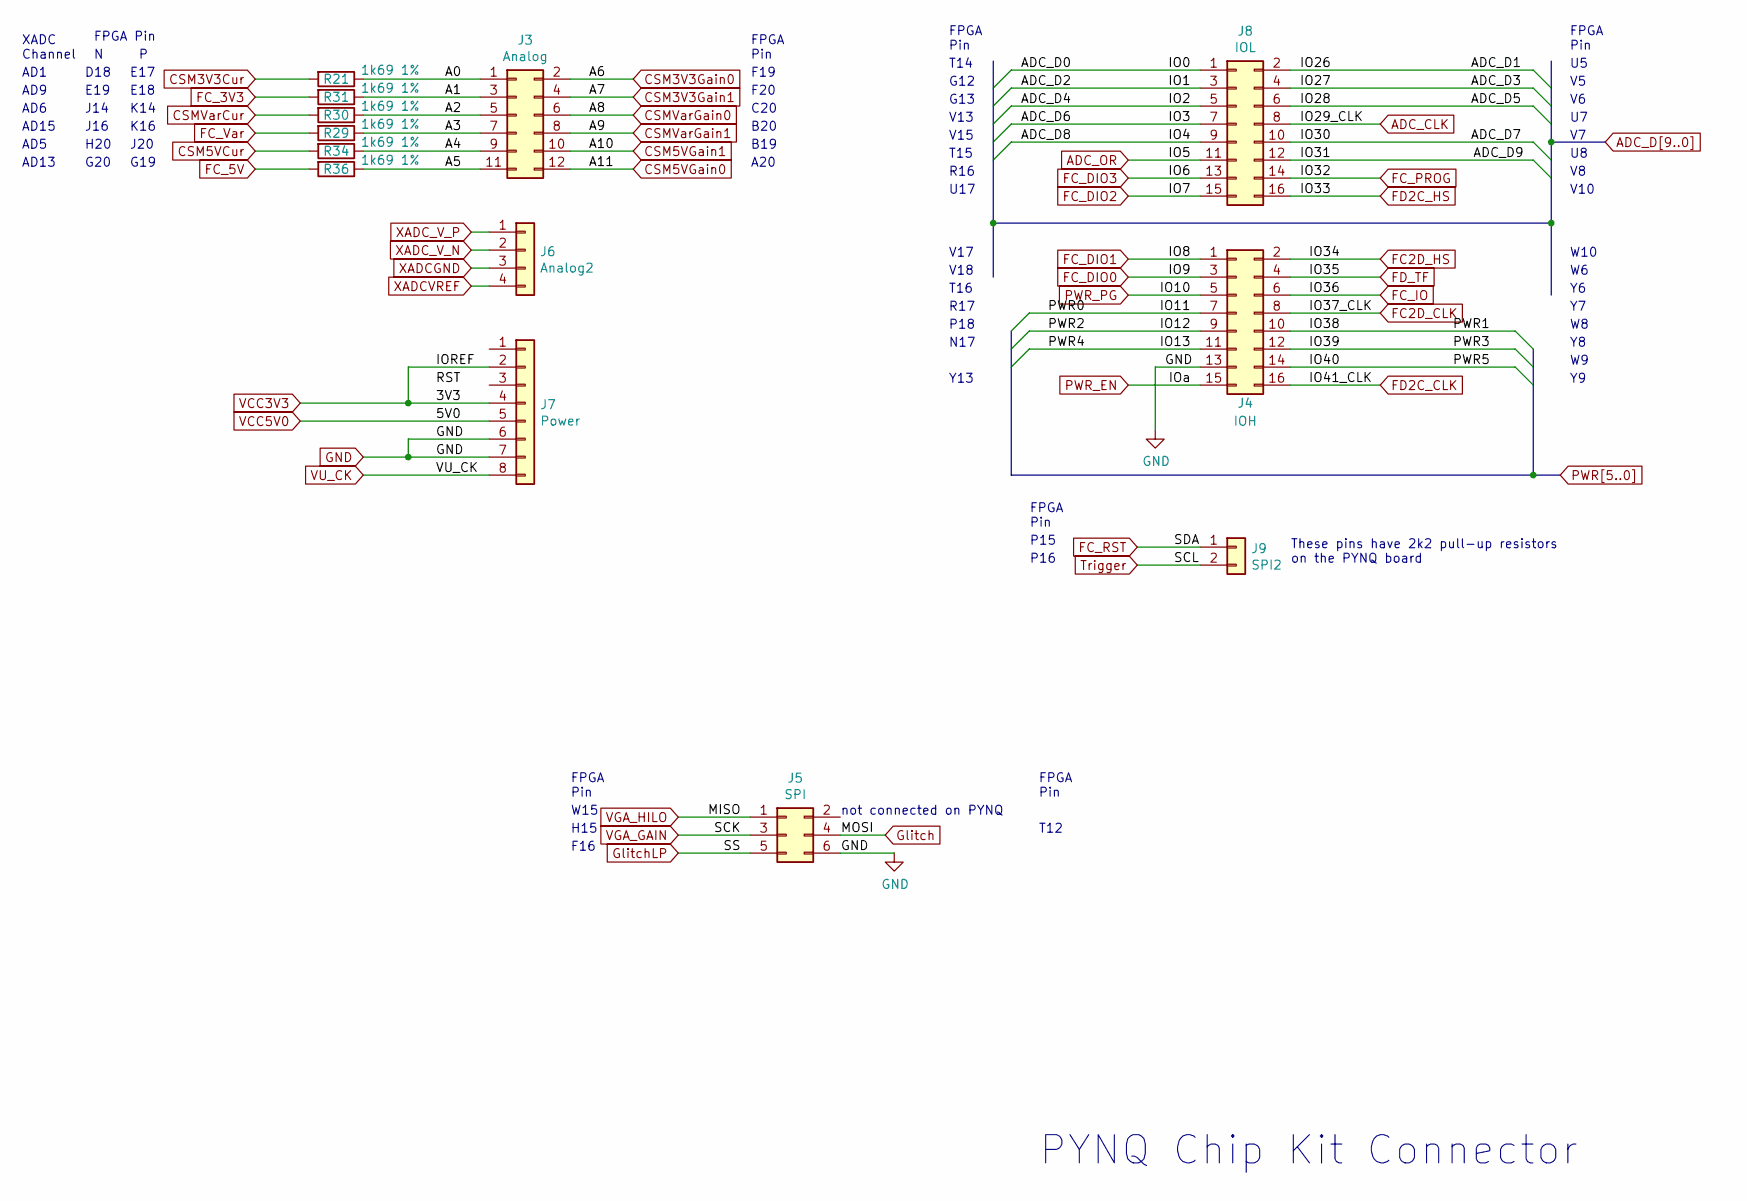
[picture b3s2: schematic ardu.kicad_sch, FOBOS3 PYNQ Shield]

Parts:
J3: Analog; PinHeader_2x06_P2.54mm_Vertical_flipped
J4: IOH; PinHeader_2x08_P2.54mm_Vertical_Flipped
J5: SPI; PinSocket_2x03_P2.54mm_Vertical
J6: Analog2; PinHeader_1x04_P2.54mm_Vertical
J7: Power; PinHeader_1x08_P2.54mm_Vertical
J8: IOL; PinHeader_2x08_P2.54mm_Vertical_Flipped
J9: SPI2; PinHeader_1x02_P2.54mm_Vertical
R21, R29, R30, R31, R34, R36: 1k69 1%; R_0603_1608Metric

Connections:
/Ardu/A0: J3.1, R21.1
/Ardu/A1: J3.3, R31.1
/Ardu/A2: J3.5, R30.1
/Ardu/A3: J3.7, R29.1
/Ardu/A4: J3.9, R34.1
/Ardu/A5: J3.11, R36.1
ADC_CLK: J8.8; also elsewhere on the board
ADC_D0: J8.1; also elsewhere on the board
ADC_D1: J8.2; also elsewhere on the board
ADC_D2: J8.3; also elsewhere on the board
ADC_D3: J8.4; also elsewhere on the board
ADC_D4: J8.5; also elsewhere on the board
ADC_D5: J8.6; also elsewhere on the board
ADC_D6: J8.7; also elsewhere on the board
ADC_D7: J8.10; also elsewhere on the board
ADC_D8: J8.9; also elsewhere on the board
ADC_D9: J8.12; also elsewhere on the board
ADC_OR: J8.11; also elsewhere on the board
CSM3V3Cur: R21.2; also elsewhere on the board
CSM3V3Gain0: J3.2; also elsewhere on the board
CSM3V3Gain1: J3.4; also elsewhere on the board
CSM5VCur: R34.2; also elsewhere on the board
CSM5VGain0: J3.12; also elsewhere on the board
CSM5VGain1: J3.10; also elsewhere on the board
CSMVarCur: R30.2; also elsewhere on the board
CSMVarGain0: J3.6; also elsewhere on the board
CSMVarGain1: J3.8; also elsewhere on the board
FC2D_CLK: J4.8; also elsewhere on the board
FC2D_HS: J4.2; also elsewhere on the board
FC_3V3: R31.2; also elsewhere on the board
FC_5V: R36.2; also elsewhere on the board
FC_DIO0: J4.3; also elsewhere on the board
FC_DIO1: J4.1; also elsewhere on the board
FC_DIO2: J8.15; also elsewhere on the board
FC_DIO3: J8.13; also elsewhere on the board
FC_IO: J4.6; also elsewhere on the board
FC_PROG: J8.14; also elsewhere on the board
FC_RST: J9.1; also elsewhere on the board
FC_Var: R29.2; also elsewhere on the board
FD2C_CLK: J4.16; also elsewhere on the board
FD2C_HS: J8.16; also elsewhere on the board
FD_TF: J4.4; also elsewhere on the board
GND: J4.13, J5.6, J7.6, J7.7; also elsewhere on the board
Glitch: J5.4; also elsewhere on the board
GlitchLP: J5.5; also elsewhere on the board
PWR0: J4.7; also elsewhere on the board
PWR1: J4.10; also elsewhere on the board
PWR2: J4.9; also elsewhere on the board
PWR3: J4.12; also elsewhere on the board
PWR4: J4.11; also elsewhere on the board
PWR5: J4.14; also elsewhere on the board
PWR_EN: J4.15; also elsewhere on the board
PWR_PG: J4.5; also elsewhere on the board
Trigger: J9.2; also elsewhere on the board
VCC3V3: J7.2, J7.4; also elsewhere on the board
VCC5V0: J7.5; also elsewhere on the board
VGA_GAIN: J5.3; also elsewhere on the board
VGA_HILO: J5.1; also elsewhere on the board
VU_CK: J7.8
XADCGND: J6.3; also elsewhere on the board
XADCVREF: J6.4
XADC_V_N: J6.2
XADC_V_P: J6.1

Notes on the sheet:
V18
H20
T12
P18
V15
V17
T14
W15
K14
FPGA Pin
E19
R16
G13
Y13
B19
B20
PYNQ Chip Kit Connector
AD6
P16
A20
XADC Channel
These pins have 2k2 pull-up resistors on the PYNQ board
AD13
V13
G20
F19
V10
T16
J16
T15
J20
F16
N17
not connected on PYNQ
J14
E18
AD9
F20
D18
AD5

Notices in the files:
hardware/fobos-dut/dut-artix7-a12t-cpg238/power.kicad_sch:
License: Apache License Version 2.0
Copyright © Cryptographic Engineering Research Group
